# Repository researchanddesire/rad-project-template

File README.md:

# PRODUCT_NAME

Starter repository template for a Research and Desire product.

Replace `PRODUCT_NAME`, `PRODUCT_REPO`, `PRODUCT_SLUG`, and
`PRODUCT_LICENSE` before publishing the repo.

## Documentation ownership

| Content | Source of truth | Published at |
| --- | --- | --- |
| Assembly guide, BOM page text, PCB overview, cable harness pages, assembly images | `assembly-docs/` in this repo | `ohai.researchanddesire.com/PRODUCT_SLUG` |
| BOM data | `hardware/bom.csv` in this repo | Rendered into assembly docs at build time |
| Hardware source assets | `hardware/cad/`, `hardware/pcb/`, `hardware/cables/` | Linked from assembly docs and BOM source fields |
| Developer notes, architecture, tests, integration behavior | `developer-docs/docs/` in this repo | `dev.researchanddesire.com/PRODUCT_SLUG` |
| End-user guides, quick starts, support docs | `simple-docs` repo | `docs.researchanddesire.com` |

The rendered BOM belongs only in the assembly docs site. Developer docs may
link to or explain the BOM workflow, but they should not embed the rendered BOM
table.

## Expected repo layout

```text
assembly-docs/
  site.yml
  nav.yml
  index.md
  pcb-overview.md
  cable-harnesses.md
  bom.md
  assembly-guide.md
  assets/
developer-docs/
  mkdocs.yml
  docs/
    .pages
    index.md
    architecture.md
    testing.md
hardware/
  bom.csv
  cad/
  cables/
  pcb/
.github/workflows/
  trigger-assembly-docs.yml
  trigger-dev-docs.yml
  generate-bom-release.yml
  bom-lint.yml
  sync-bom-schema.yml
```

## Setup checklist

1. Replace placeholders throughout this template.
2. Replace `assembly-docs/site.yml` with real `slug`, `title`, `license`, and
   `nav_order` values.
3. Add the GitHub topic `ohai-assembly-docs` only after placeholders are gone
   and local assembly/build checks pass. Do not add this topic to the template.
4. Configure `DOCS_DISPATCH_TOKEN` in this product repo so product pushes can
   dispatch rebuilds to `assembly-docs` and `dev-docs`. The default
   `GITHUB_TOKEN` cannot trigger these cross-repo rebuild workflows.
5. Keep `.github/workflows/scripts/bom.schema.json` synced from `dev-docs`;
   do not edit it by hand.
6. Add user-facing pages directly to `simple-docs`, then link them from this
   repo if useful.

## Required Secrets

`DOCS_DISPATCH_TOKEN` must be a fine-grained PAT or organization secret with
permission to send `repository_dispatch` events to:

- `researchanddesire/assembly-docs`
- `researchanddesire/dev-docs`

The dispatch workflows use this secret because a product repo's default
`GITHUB_TOKEN` is scoped to that product repo and cannot reliably start
workflows in sibling repositories.

## Local docs preview

Preview developer docs from this repo:

```bash
cd developer-docs
pip install -r requirements.txt 2>/dev/null || pip install mkdocs mkdocs-material mkdocs-awesome-pages-plugin
mkdocs serve
```

Preview the assembled sites from the aggregator repos:

```bash
cd ../assembly-docs
ASSEMBLE_LOCAL="$HOME/Github" ./scripts/assemble-docs.sh
mkdocs serve

cd ../dev-docs
ASSEMBLE_LOCAL="$HOME/Github" ./scripts/assemble-docs.sh
mkdocs serve
```

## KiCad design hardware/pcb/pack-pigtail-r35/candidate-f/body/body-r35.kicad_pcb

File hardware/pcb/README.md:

# PCB sources

**Current local pack-interface variant: R35F**, `pack-pigtail-r35/candidate-f/`.
It replaces the body J2 header with five copper solder lands, preserving the
four logical signals and adding a separate sensor-return landing. Native body
DRC0/0/0, 94components/338nodes and other footprint poses/pads/routes/rules are
reviewed; flange PCB bytes equal R28S. See [the variant record](pack-pigtail-r35/README.md).
This is matched to R34 pigtail J, not a full harness or fabrication release.
R28S below remains the preserved header-based baseline.

**Current review package: R28S**, `flange-access-r28/candidate-s/`, with full native system/body/flange projects and13source sheets. The body stays R23D; the flange is repaired around the edge-facing J1/J7 headers. Both native DRC reports are0/0/0;94components/338nodes and physical poses are conserved. It matches the R27D cradle envelope. Actual wiring/buttons/seals, fresh GUI ERC, supplier/current CAM and physical checks remain open. Battery OPEN/BOM unchanged.

## Preserved sources

**Current routed electrical baseline:** R23D (`stackup-r23/candidate-d/`)
completes the six-layer body with zero native DRC/unconnected/footprint
findings and preserves the routed four-layer flange. Fresh GUI ERC,
supplier/current CAM and electrical/physical review remain open.

**Plug-access correction in progress:** `flange-access-r28/candidate-a/`
turns J1/J7 toward board edges, conserving all24part/pad maps and22other
poses. Nominal component/courtyard/plug-approach screens clear, and R27D
binds those poses in native CAD. Source copper is reference only: native
DRC78/unconnected11/footprint0. Repair routing before fabrication outputs;
R23's old flange pass does not transfer to the new header poses. Semi-flex
remains allowed but is not already implemented. Battery OPEN/BOM unchanged.

Earlier checkpoints below are preserved source history.

**Preserved placement:** [R16 candidate U](route-r16/README.md) repacks the body
power/logic groups and moves F1/D1 to the flange. All 89 main parts remain,
65 body / 24 flange. Fresh flange native routing findings are 0/0/0; the body
has 163 missing connections. Fourteen candidate package changes and two header
input-net changes are explicit. Fresh R16 GUI ERC, carrier plug openings and
the complete prototype integration remain unfinished; battery stays OPEN.

**Preserved layout checkpoint:** [R15 candidate T](route-r15/README.md) has the
routed 22-part flange with native zero DRC/unconnected/footprint findings.
The 67-part body remains byte-identical to R14B and has 165 open connections.
R15 repacks the flange, changes J1 to an SH2 candidate and conserves all
device pin/net identities. Fresh R15 GUI ERC and actual harness/process/RF
acceptance remain open. The R14/R12 material below is preserved source history.

**Current circuit source:** [R14 candidate B](split-r14/README.md) contains
body/flange native schematic/project/PCB sets plus a full-device root. Native
ERC reports zero errors/warnings across13 sheets; original318 pin nets plus20
header nodes match. Instance binding preserves all R12 board content apart
from context paths. Both PCBs remain unrouted with165/81 open connections.

**Physical placement source:** [R12 candidate I](split-r12/README.md) contains separate
native body and flange placement files: 67/22 footprints including two new
interboard headers. Pad/net parity and native placement checks pass; 165/81
connections remain unrouted. R14 adds native schematics; actual supported
wiring remains open. The T-boards below remain preserved electrical baselines;
their checks do not transfer to new outlines or partitions. The existing remote
tip island would make three rigid boards total unless integrated later. See
[the front-loading study](../../developer-docs/docs/archive/front-load-study-r9.md).

The preserved [R0 native KiCad schematic](prototype-r0/buttplug-r0.kicad_sch) is a
new connected six-sheet circuit informed by Lucy and Gaby's
[reference screenshot](reference/lucy-gaby-schematic.png). Local symbols,
manifest, netlist, ERC evidence and review plots live beside it. See the
[electronics record](../../developer-docs/docs/archive/electronics-prototype-r0.md).

The [main T-board](prototype-r0/buttplug-r0.kicad_pcb) now has 87 physical
component footprints and complete routing under its study rules. Both main
and tip boards have zero native DRC violations and unconnected pads, with
independent digital reviews. The main
[layout record](../../developer-docs/docs/archive/pcb-layout-r0.md) reports the exact
current routing and DRC state; do not infer a fabrication release from presence
of a board file. The [remote TMP117 board](tip-r1/buttplug-tip-r1.kicad_pcb)
is a separate 6×4 mm island.
Remote parts remain excluded from main-board transfer.

R2's selected 15 mm neck needs a centered, component-free board waist and
fresh component placement. Preserve R0 and its review records as the electrical
baseline; their passing checks do not apply to a revised outline or routing.
The single T topology was the R2 direction; R9 now explores separate body/flange boards.

The separate [R2 main project](prototype-r2/README.md) now has a routed candidate
with 87 footprints, 48 nets, exact 310-pad circuit parity and native zero DRC,
unconnected or footprint findings. Read its own `layout-validation-r2.json`
and review/reproduction records. The 8 mm waist is component-free. The frozen
unrouted placement remains separate with 236 unconnected items; its report
does not describe later copper or pose changes. No fabrication release exists.

The [assembly-process review](../../developer-docs/docs/archive/pcb-assembly-process-r1.md)
marks the exact U1/U5 under-paste drill locations, U6 center-paste omission and
U7 provisional lands. Native detail polygons, primary-reference hashes and
location-specific questions are indexed in
`hardware/design/pcb-assembly-process-r1.json`. This is assembler-review input;
the board, parts, stencil/via process and BOM remain unapproved.

Frozen review packets now live under
[`prototype-r2/fabrication-review-r1/`](prototype-r2/fabrication-review-r1/review-note.md)
and [`tip-r1/fabrication-review-r1/`](tip-r1/fabrication-review-r1/review-note.md).
Each binds the exact native source and local libraries to plotted copper,
mask, outline, drills and placement data, with parsed CAM checks and previews.
Paste is separated in `paste-review-UNAPPROVED/`. These packets are for
fabricator/assembler review; stackup, finish, stencil/via treatment, actual
parts and placement-machine conventions still need acceptance.

Parts, assembly process, full mechanical fit, RF and physical operation remain
review gates. No fabrication package is released. The human-owned product BOM
is unchanged. `concepts/` retains the historical outline-only board.

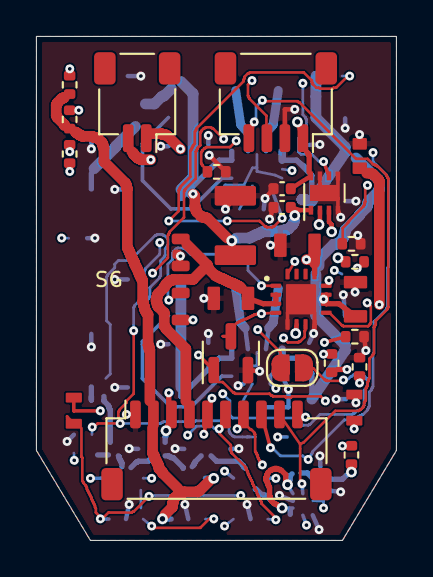
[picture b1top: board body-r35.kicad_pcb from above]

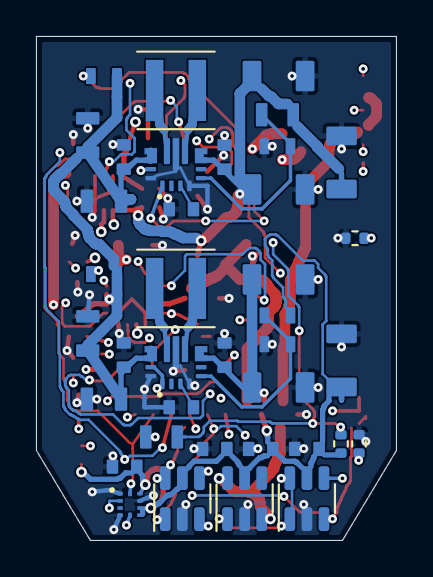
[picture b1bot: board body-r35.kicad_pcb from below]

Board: 6 copper layers, 20.0 x 28.0 mm, 65 parts (38 on the bottom side), 36 nets.

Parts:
C1, C2: GRM21BR71A475KA73L; Murata_GRM21_0805_Reflow
C3, C11, C12, C21, C22: GRM21BR61A106KE19L; Murata_GRM21_0805_Reflow
C13, C14, C15, C23, C24, C25: GRM31CR71A226KE15L; Murata_GRM31_1206_Reflow
C16, C26, C27, C41, C42, C43, C44: GRM188R71C104KA01D; Murata_GRM18_0603_Reflow
C28, C29: GRM155R71C104KA88D candidate; C_0402_1005Metric
C30: GRM32ER61A476KE20L; Murata_GRM32_1210_Reflow
C51, C52, C53, C54: C1608X5R1A106K080AC; TDK_C1608_0603_Reflow
J2: PACK_PIGTAIL_4NET_5LAND; Pack_Pigtail_4Net_5Land
J3: SM02B-SRSS-TB; JST_SH_SM02B-SRSS-TB_1x02-1MP_P1.00mm_Horizontal
J5: SM04B-SRSS-TB; JST_SH_SM04B-SRSS-TB_1x04-1MP_P1.00mm_Horizontal
J6: SM10B-SRSS-TB candidate; JST_SH_SM10B-SRSS-TB_1x10-1MP_P1.00mm_Horizontal
JP1: PCB solder jumper / open; SolderJumper-2_P1.3mm_Open_RoundedPad1.0x1.5mm
L1, L2: XFL4020-152MEC; L_Coilcraft_XxL4020
Q1: AO3400A; SOT-23
R1: TNPW04028K87BEED; R_0402_1005Metric
R2: TNPW04023K24BEED; R_0402_1005Metric
R3, R4, R5, R42: TNPW040210K0BEED; R_0402_1005Metric
R11: TNPW0603312KBEEA; Vishay_TNPW0603_IEC_Reflow
R12, R22: TNPW0603100KBEEA; Vishay_TNPW0603_IEC_Reflow
R13, R26: TNPW060310K0BEEA; Vishay_TNPW0603_IEC_Reflow
R21: TNPW0805362KBEEA; Vishay_TNPW0805_IEC_Reflow
R23, R24, R25, R48: TNPW0402100KBEED; R_0402_1005Metric
R41: TNPW04024K70BEED; R_0402_1005Metric
R43: TNPW0805715KBEEA; Vishay_TNPW0805_IEC_Reflow
R44: TNPW0603110KBEEA; Vishay_TNPW0603_IEC_Reflow
R45: TNPW0603200KBEEA; Vishay_TNPW0603_IEC_Reflow
R46: TNPW040211K0BEED; R_0402_1005Metric
R47: TNPW04021K00BEED; R_0402_1005Metric
U1: BQ24074RGT; TI_RGT0016C_3x3mm_BQ24074_EP1.68mm
U2, U3: TPS63070RNM; TI_RNM0015A_2.5x3mm_TPS63070
U4: SN74LVC1G11DBVR; SOT-23-6
U5: DRV8212DSGR; WSON-8-1EP_2x2mm_P0.5mm_EP0.9x1.6mm
U7: MC3635; MEMSIC_MC3635_LGA10_1.6x1.6mm_P0.4mm
U8: TPS3700DDCR; TSOT-23-6
U9: TPS3808G33DBVR; SOT-23-6

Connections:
3V3: C13.1, C14.1, C15.1, C27.1, C29.1, C41.1, C42.1, C43.1, C52.1, J5.1, J6.3, R4.1, R5.1, R11.1, R41.1, R42.1, U2.7, U2.8, U4.5, U5.8, U7.6, U7.7, U7.9, U8.5, U9.5
ACCEL_INT_N: J6.10, R41.2, U7.5
CHARGE_CE_N: Q1.3, R3.2, U1.4
CHARGE_GATE: Q1.1, R47.2, R48.1
CHARGE_PERMIT: JP1.2, R47.1
CHARGE_STATUS_N: R5.2, U1.9
CHARGE_TEMP_OK: JP1.1, R46.2, U8.1, U8.6, U9.1
CHG_ILIM: R2.1, U1.12
CHG_ISET: R1.1, U1.16
DOCK_PRESENT_N: J6.7, R4.2, U1.7, U4.6
GND: C1.2, C2.2, C3.2, C11.2, C12.2, C13.2, C14.2, C15.2, C16.2, C21.2, C22.2, C23.2, C24.2, C25.2, C26.2, C27.2, C28.2, C29.2, C30.2, C41.2, C42.2, C43.2, C44.2, C51.2, C52.2, C53.2, C54.2, J2.2, J5.2, J6.1, Q1.2, R1.2, R2.2, R12.2, R22.2, R23.2, R24.2, R25.2, R45.2, R48.2, U1.5, U1.8, U1.17, U2.4, U2.10, U2.15, U3.4, U3.10, U3.15, U4.2, U5.4, U5.5, U5.7, U5.9, U7.1, U7.4, U7.8, U8.2, U9.2
I2C_SCL: J5.4, J6.9, U7.10
I2C_SDA: J5.3, J6.8, U7.2
MOTOR_3V7: C23.1, C24.1, C25.1, C28.1, C30.1, C54.1, R21.1, U3.7, U3.8, U5.1
MOTOR_ARM: J6.5, R23.1, U3.14, U4.3
MOTOR_IN1: R25.1, U4.4, U5.6
MOTOR_N: J3.2, U5.3
MOTOR_P: J3.1, U5.2
MOTOR_PWM: J6.6, R24.1, U4.1
PACK_GUARD: J2.4, R42.2, R43.1
PACK_NTC: J2.3, U1.1
PACK_P: C2.1, J2.1, J6.4, U1.2, U1.3
REG1_AUX: C16.1, U2.3
REG1_FB: R11.2, R12.1, U2.5
REG1_L1: L1.1, U2.11
REG1_L2: L1.2, U2.9
REG1_PS: R13.2, U2.1, U2.14
REG2_AUX: C26.1, U3.3
REG2_FB: R21.2, R22.1, U3.5
REG2_L1: L2.1, U3.11
REG2_L2: L2.2, U3.9
REG2_PS: R26.2, U3.1
SYS: C3.1, C11.1, C12.1, C21.1, C22.1, C51.1, C53.1, R13.1, R26.1, U1.10, U1.11, U2.12, U2.13, U3.12, U3.13
TEMP_COLD_IN: R44.2, R45.1, U8.4
TEMP_HOT_IN: R43.2, R44.1, U8.3
VBUS_CHG: C1.1, C44.1, J6.2, R3.1, R46.1, U1.6, U1.13, U9.3, U9.6

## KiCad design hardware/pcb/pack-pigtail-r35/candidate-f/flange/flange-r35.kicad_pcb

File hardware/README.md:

# Hardware

This folder contains human-owned hardware source files for PRODUCT_NAME.

## BOM

`bom.csv` is the single source of truth for the product-level bill of materials.
It is edited by humans and validated by `bom-lint`.

The assembly docs site renders this CSV into `assembly-docs/bom.md` at assemble
time. Do not commit a generated rendered table here.

## Folders

- `cad/`: mechanical source files and exports.
- `pcb/`: PCB source files, fabrication notes, and production exports.

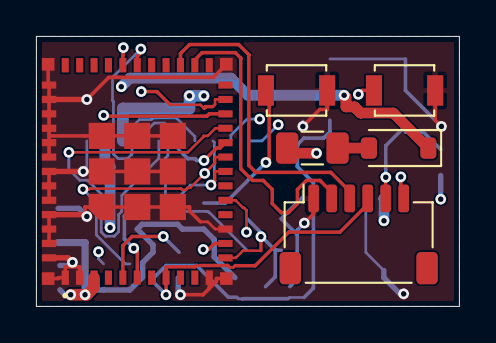
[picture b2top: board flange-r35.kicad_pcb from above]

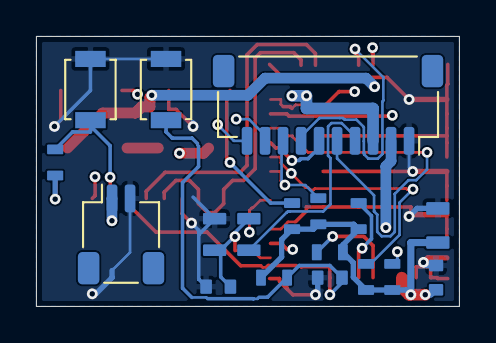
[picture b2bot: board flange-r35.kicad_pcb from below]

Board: 4 copper layers, 23.5 x 15.0 mm, 24 parts (18 on the bottom side), 22 nets.

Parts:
C31: GRM21BR61A106KE19L; Murata_GRM21_0805_Reflow
C32, C34: GRM188R71C104KA01D; Murata_GRM18_0603_Reflow
C33: C1608X7R1E105K080AB; TDK_C1608_0603_Reflow
D1: B140HW-7; Diodes_B140HW_SOD123_A1_K2
F1: 1206L050YR; Fuse_1206_3216Metric
J1: SM02B-SRSS-TB; JST_SH_SM02B-SRSS-TB_1x02-1MP_P1.00mm_Horizontal
J4: SM06B-SRSS-TB; JST_SH_SM06B-SRSS-TB_1x06-1MP_P1.00mm_Horizontal
J7: SM10B-SRSS-TB candidate; JST_SH_SM10B-SRSS-TB_1x10-1MP_P1.00mm_Horizontal
R31, R32, R33, R34, R35, R36: TNPW060310K0BEEA; Vishay_TNPW0603_IEC_Reflow
R37, R38: TNPW06034K70BEEA; Vishay_TNPW0603_IEC_Reflow
R39, R40: TNPW08051M00BEEA; Vishay_TNPW0805_IEC_Reflow
SW1, SW2, SW3, SW4: B3U-1000P; SW_SPST_B3U-1000P
U6: ESP32-C3-MINI-1-N4X; Espressif_ESP32-C3-MINI-1_53Pads

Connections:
3V3: C31.1, C32.1, J7.3, R31.1, R32.1, R33.1, R34.1, R35.1, R36.1, R37.1, R38.1, U6.3
ACCEL_INT_N: J7.10, U6.16
BOOT_N: J4.5, R34.2, SW4.1, U6.23
DOCK_5V: F1.1, J1.1
DOCK_FUSED: D1.1, F1.2
DOCK_PRESENT_N: J7.7, U6.30
GND: C31.2, C32.2, C33.2, C34.2, J1.2, J4.1, J7.1, R40.2, SW1.2, SW2.2, SW3.2, SW4.2, U6.1, U6.2, U6.11, U6.14, U6.36, U6.37, U6.38, U6.39, U6.40, U6.41, U6.42, U6.43, U6.44, U6.45, U6.46, U6.47, U6.48, U6.49, U6.50, U6.51, U6.52, U6.53
I2C_SCL: J7.9, R38.2, U6.19
I2C_SDA: J7.8, R37.2, U6.18
MCU_EN: C33.1, J4.4, R31.2, SW3.1, U6.8
MODE_N: R36.2, SW2.1, U6.6
MOTOR_ARM: J7.5, U6.21
MOTOR_PWM: J7.6, U6.20
PACK_P: J7.4, R39.1
POWER_N: R35.2, SW1.1, U6.13
STRAP2: R32.2, U6.5
STRAP8: R33.2, U6.22
UART_TX: J4.6, U6.31
USB_DM: J4.2, U6.26
USB_DP: J4.3, U6.27
VBAT_ADC: C34.1, R39.2, R40.1, U6.12
VBUS_CHG: D1.2, J7.2

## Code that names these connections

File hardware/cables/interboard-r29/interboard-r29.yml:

metadata:
  title: R29 body to flange harness - prototype starting blanks
  description: Ten numbered conductors, J6 to J7, following the unchanged R28S native net map.
  notes: 120 mm starting blanks; trim on the assembly fixture. This is not a finished cable length or order release.
options:
  fontname: Arial
  color_mode: FULL
connectors:
  J6:
    type: Wire-side JST SH10 candidate
    subtype: Without protrusions - 11 mm housing width
    manufacturer: JST
    mpn: SHR-10V-S
    pincount: 10
    pinlabels: [GND, VBUS_CHG, 3V3, PACK_P, MOTOR_ARM, MOTOR_PWM, DOCK_PRESENT_N, I2C_SDA, I2C_SCL, ACCEL_INT_N]
    notes: "Body header SM10B-SRSS-TB candidate. Numeric pin view, not a mating-face drawing.\nUse SSH-003T-P0.2-H contacts with reviewed tooling/crimp.\nThe 13 mm SHR-10V-S-B is not interchangeable with the modeled 11 mm allowance."
  J7:
    type: Wire-side JST SH10 candidate
    subtype: Without protrusions - 11 mm housing width
    manufacturer: JST
    mpn: SHR-10V-S
    pincount: 10
    pinlabels: [GND, VBUS_CHG, 3V3, PACK_P, MOTOR_ARM, MOTOR_PWM, DOCK_PRESENT_N, I2C_SDA, I2C_SCL, ACCEL_INT_N]
    notes: "Flange header SM10B-SRSS-TB candidate. Verify pin 1 independently at both ends.\nDo not assume visual left-to-right order stays the same on the rotated board."
cables:
  W-INTERBOARD-R29:
    category: bundle
    type: Ten independent wires - fixture trim
    manufacturer: Accu-Glass
    mpn: '100690'
    gauge: 28
    gauge_unit: AWG
    wirecount: 10
    colors: [BN, BN, BN, BN, BN, BN, BN, BN, BN, BN]
    wirelabels: ['1/GND', '2/VBUS_CHG', '3/3V3', '4/PACK_P', '5/MOTOR_ARM', '6/MOTOR_PWM', '7/DOCK_PRESENT_N', '8/I2C_SDA', '9/I2C_SCL', '10/ACCEL_INT_N']
    length: 0.120
    length_unit: m
    notes: "120 mm STARTING BLANK each; trim using the route fixture. Removed excess is not service slack.\nAmber Kapton candidate; labels identify nets, not supplied jacket colours.\nOD0.60 and centerline R4.0 are separate design allowances, not controlled maker maxima.\nStatic routing and supported assembly/service movement must be reviewed before finishing both ends."
connections:
  - - J6: [1, 2, 3, 4, 5, 6, 7, 8, 9, 10]
    - W-INTERBOARD-R29: [1, 2, 3, 4, 5, 6, 7, 8, 9, 10]
    - J7: [1, 2, 3, 4, 5, 6, 7, 8, 9, 10]
additional_bom_items:
  - description: SH crimp contact candidate - verify produced crimp
    qty: 20
    unit: pcs
    manufacturer: JST
    mpn: SSH-003T-P0.2-H
tweak:
  append: 'graph [label="R29 / PROTOTYPE STARTING MATERIAL\n120 mm blanks trimmed to fixture; no finished length or physical fit acceptance", labelloc=t, labeljust=l, fontsize=18, fontname="Arial"];'

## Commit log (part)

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2026-06-15 Initial R+D project template
2026-06-16 Update Ohai product template standard
